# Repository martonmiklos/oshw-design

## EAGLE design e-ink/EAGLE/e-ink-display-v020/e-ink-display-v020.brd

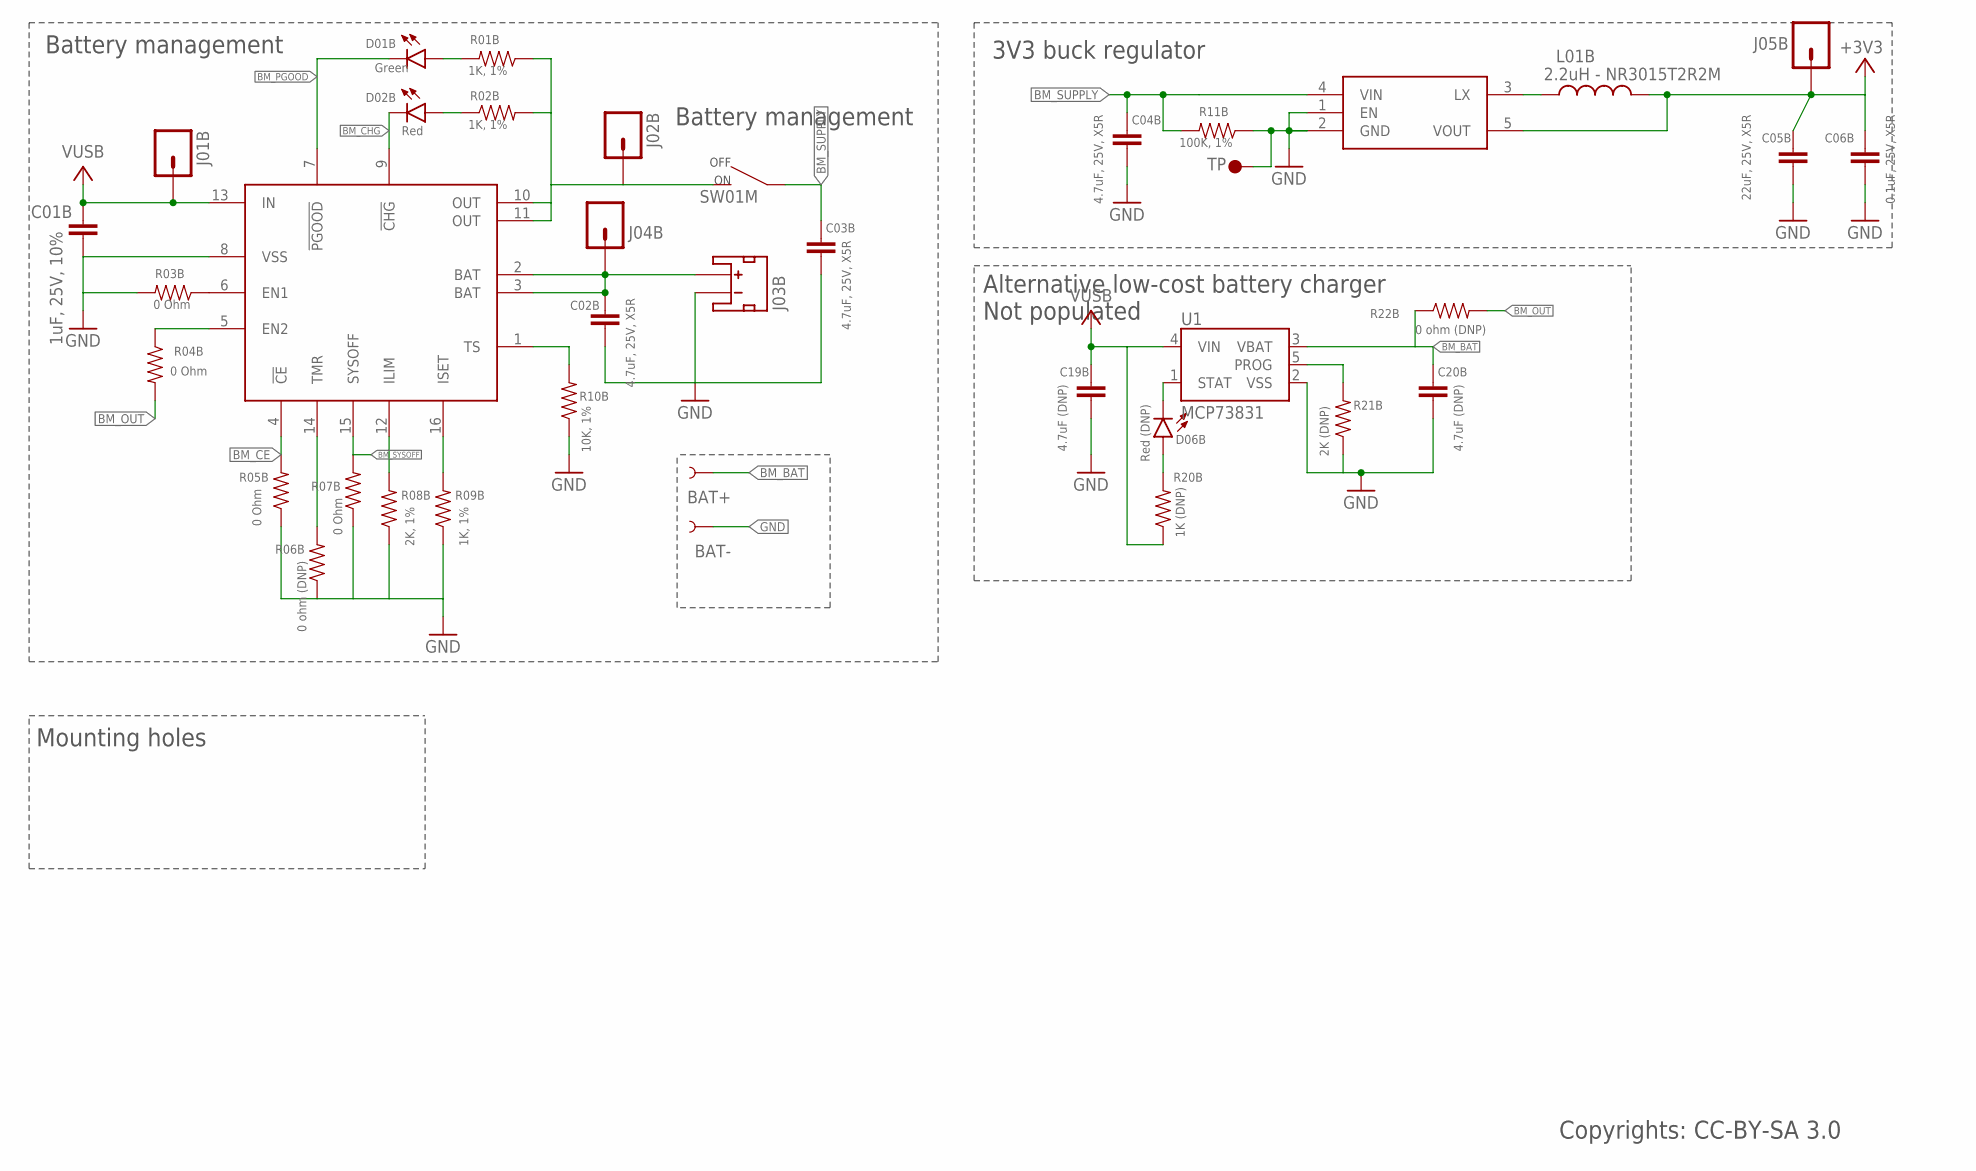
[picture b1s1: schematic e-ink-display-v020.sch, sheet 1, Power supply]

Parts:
BAT+: TEST-POINTSQ_THRU; TP-SQ_15TH
BAT-: TEST-POINTRD_THRU; TP-RD_15TH
C01B: 1uF, 25V, 10%; 0603-CAP
C02B, C03B, C04B: 4.7uF, 25V, X5R; 0603-CAP
C05B: 22uF, 25V, X5R; 0603-CAP
C06B: 0.1uF, 25V, X5R; 0603-CAP
C19B, C20B: 4.7uF (DNP); 0603-CAP
D01B: Green; LED-0603
D02B: Red; LED-0603
D06B: Red (DNP); LED-0603
J01B, J02B, J04B, J05B: M01PTH; 1X01
J03B: JST_2MM_MALE; JST-2-SMD
L01B: 2.2uH - NR3015T2R2M; INDUCTOR-NR3015
R01B, R02B, R09B: 1K, 1%; 0603-RES
R03B, R04B, R05B, R07B: 0 Ohm; 0603-RES
R06B: 0 ohm (DNP); 0603-RES
R08B: 2K, 1%; 0603-RES
R10B: 10K, 1%; 0603-RES
R11B: 100K, 1%; 0603-RES
R20B: 1K (DNP); 0603-RES
R21B: 2K (DNP); 0603-RES
R22B: 0 ohm (DNP); 1206
SW01M: SWITCHSIDE-SLIDE; SW-SPDT-TH
TP01B: TP1; TP35_BOT
U1: MCP73831; SOT23-5
U01B: BQ24075; PVQFN-16
U02B: R8008-33; SOT23-5

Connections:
+3V3: C05B.2, C06B.2, J05B.1, L01B.2, U02B.5 (VOUT); also elsewhere on the board
BM_BAT: BAT+.P$1, C02B.2, C20B.2, J03B.2 (+), J04B.1, R22B.1, U1.3 (VBAT), U01B.2 (BAT), U01B.3 (BAT)
BM_CE: R05B.2, U01B.4 (!CE)
BM_CHG: D02B.C, U01B.9 (!CHG); also elsewhere on the board
BM_OUT: J02B.1, R01B.1, R02B.2, R04B.2, R22B.2, SW01M.2, U01B.10 (OUT), U01B.11 (OUT)
BM_PGOOD: D01B.C, U01B.7 (!PGOOD); also elsewhere on the board
BM_SUPPLY: C03B.2, C04B.2, R11B.2, SW01M.1, U02B.4 (VIN); also elsewhere on the board
BM_SYSOFF: R07B.2, U01B.15 (SYSOFF)
GND: BAT-.P$1, C01B.1, C02B.1, C03B.1, C04B.1, C05B.1, C06B.1, C19B.1, C20B.1, J03B.1 (-), R03B.2, R05B.1, R06B.1, R07B.1, R08B.1, R09B.1, R10B.1, R11B.1, R21B.1, TP01B.P$1, U1.2 (VSS), U01B.8 (VSS), U02B.1 (EN), U02B.2 (GND); also elsewhere on the board
unnamed: R08B.2, U01B.12 (ILIM)
unnamed: R09B.2, U01B.16 (ISET)
unnamed: R04B.1, U01B.5 (EN2)
unnamed: R03B.1, U01B.6 (EN1)
unnamed: R06B.2, U01B.14 (TMR)
unnamed: R10B.2, U01B.1 (TS)
unnamed: D02B.A, R02B.1
unnamed: D01B.A, R01B.2
unnamed: R21B.2, U1.5 (PROG)
unnamed: L01B.1, U02B.3 (LX)
unnamed: D06B.C, U1.1 (STAT)
unnamed: D06B.A, R20B.2
VUSB: C01B.2, C19B.2, J01B.1, R20B.1, U1.4 (VIN), U01B.13 (IN); also elsewhere on the board

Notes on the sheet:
Battery management
3V3 buck regulator
Mounting holes
Alternative low-cost battery charger Not populated
Copyrights: CC-BY-SA 3.0

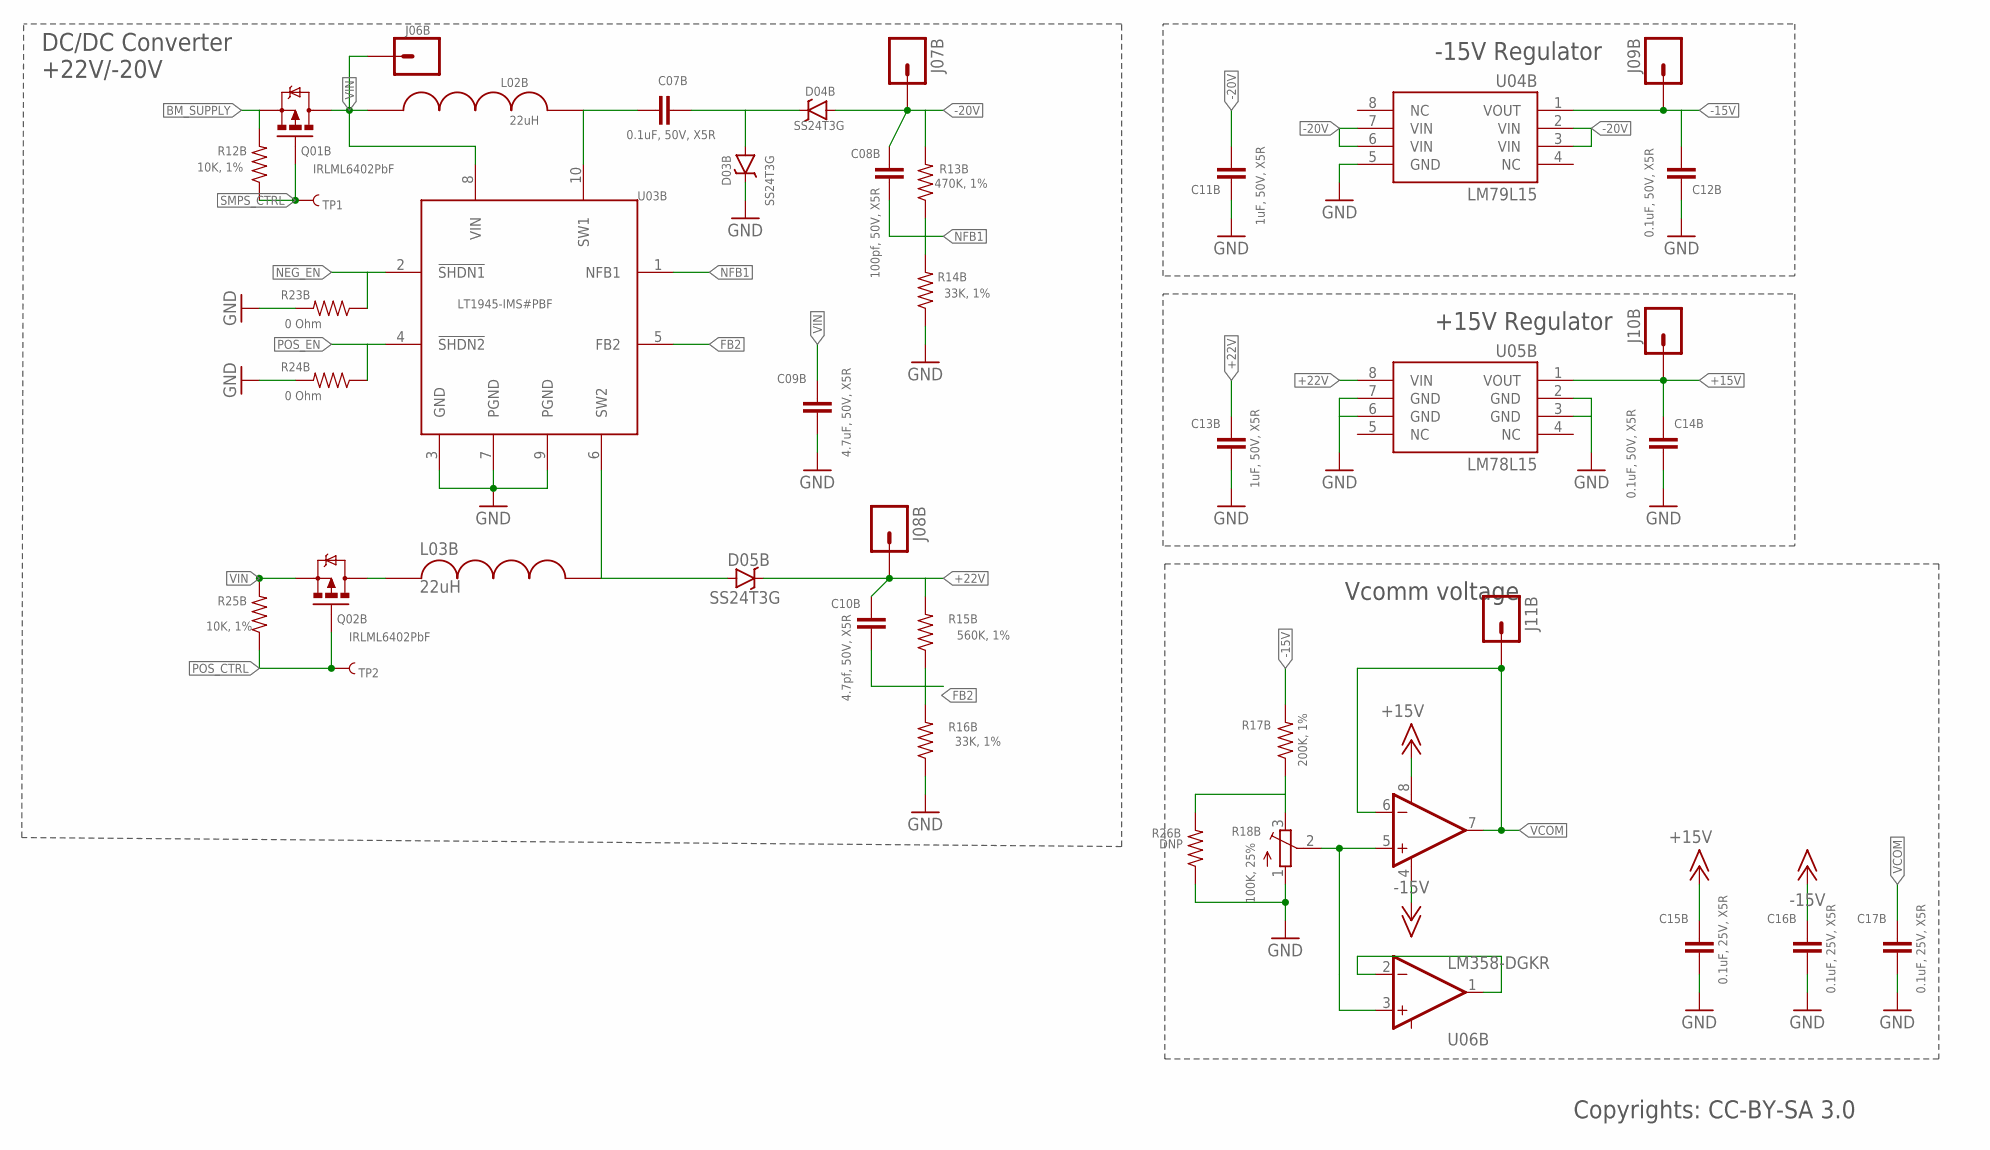
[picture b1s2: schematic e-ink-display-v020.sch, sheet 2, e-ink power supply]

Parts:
C07B, C12B, C14B: 0.1uF, 50V, X5R; 0603-CAP
C08B: 100pf, 50V, X5R; 0603-CAP
C09B: 4.7uF, 50V, X5R; 0603-CAP
C10B: 4.7pf, 50V, X5R; 0603-CAP
C11B, C13B: 1uF, 50V, X5R; 0603-CAP
C15B, C16B, C17B: 0.1uF, 25V, X5R; 0603-CAP
D03B, D04B, D05B: SS24T3G; SMA-DIODE
J06B, J07B, J08B, J09B, J10B, J11B: M01PTH; 1X01
L02B, L03B: 22uH; 4040(1515)
Q01B, Q02B: IRLML6402PbF; SOT23-3
R12B, R25B: 10K, 1%; 0603-RES
R13B: 470K, 1%; 0603-RES
R14B, R16B: 33K, 1%; 0603-RES
R15B: 560K, 1%; 0603-RES
R17B: 200K, 1%; 0603-RES
R18B: 100K, 25%; TC33X
R23B, R24B: 0 Ohm; 0603-RES
R26B: DNP; 0603-RES
TP1, TP2: TEST-POINTRD_THRU; TP-RD_15TH
U03B: LT1945-IMS#PBF; MSOP-10
U04B: LM79L15; SO08
U05B: LM78L15; SO08
U06B: LM358-DGKR; MSOP-8

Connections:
+15V: C14B.2, C15B.2, J10B.1, U05B.1 (VOUT), U06B.8 (V+); also elsewhere on the board
+22V: C10B.2, C13B.2, D05B.C, J08B.1, R15B.2, U05B.8 (VIN); also elsewhere on the board
-15V: C12B.2, C16B.2, J09B.1, R17B.2, U04B.1 (VOUT), U06B.4 (V-); also elsewhere on the board
-20V: C08B.2, C11B.2, D04B.A, J07B.1, R13B.2, U04B.2 (VIN), U04B.3 (VIN), U04B.6 (VIN), U04B.7 (VIN); also elsewhere on the board
BM_SUPPLY: Q01B.2 (S), R12B.2; also elsewhere on the board
FB2: C10B.1, R15B.1, R16B.2, U03B.5 (FB2)
GND: C09B.1, C11B.1, C12B.1, C13B.1, C14B.1, C15B.1, C16B.1, C17B.1, D03B.C, R14B.1, R16B.1, R18B.1 (A), R23B.2, R24B.2, R26B.1, U03B.3 (GND), U03B.7 (PGND), U03B.9 (PGND), U04B.5 (GND), U05B.2 (GND), U05B.3 (GND), U05B.6 (GND), U05B.7 (GND); also elsewhere on the board
unnamed: C07B.1, L02B.P$2, U03B.10 (SW1)
unnamed: C07B.2, D03B.A, D04B.C
unnamed: R18B.2 (S), U06B.3 (+IN1), U06B.5 (+IN2)
unnamed: D05B.A, L03B.P$2, U03B.6 (SW2)
unnamed: U06B.1 (OUT1), U06B.2 (-IN1)
unnamed: L03B.P$1, Q02B.3 (D)
unnamed: R17B.1, R18B.3 (E), R26B.2
NEG_EN: R23B.1, U03B.2 (!SHDN1); also elsewhere on the board
NFB1: C08B.1, R13B.1, R14B.2, U03B.1 (NFB1)
POS_CTRL: Q02B.1 (G), R25B.1, TP2.P$1; also elsewhere on the board
POS_EN: R24B.1, U03B.4 (!SHDN2); also elsewhere on the board
SMPS_CTRL: Q01B.1 (G), R12B.1, TP1.P$1; also elsewhere on the board
VCOM: C17B.2, J11B.1, U06B.6 (-IN2), U06B.7 (OUT2); also elsewhere on the board
VIN: C09B.2, J06B.1, L02B.P$1, Q01B.3 (D), Q02B.2 (S), R25B.2, U03B.8 (VIN)

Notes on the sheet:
-15V Regulator
+15V Regulator
Vcomm voltage
DC/DC Converter +22V/-20V
Copyrights: CC-BY-SA 3.0

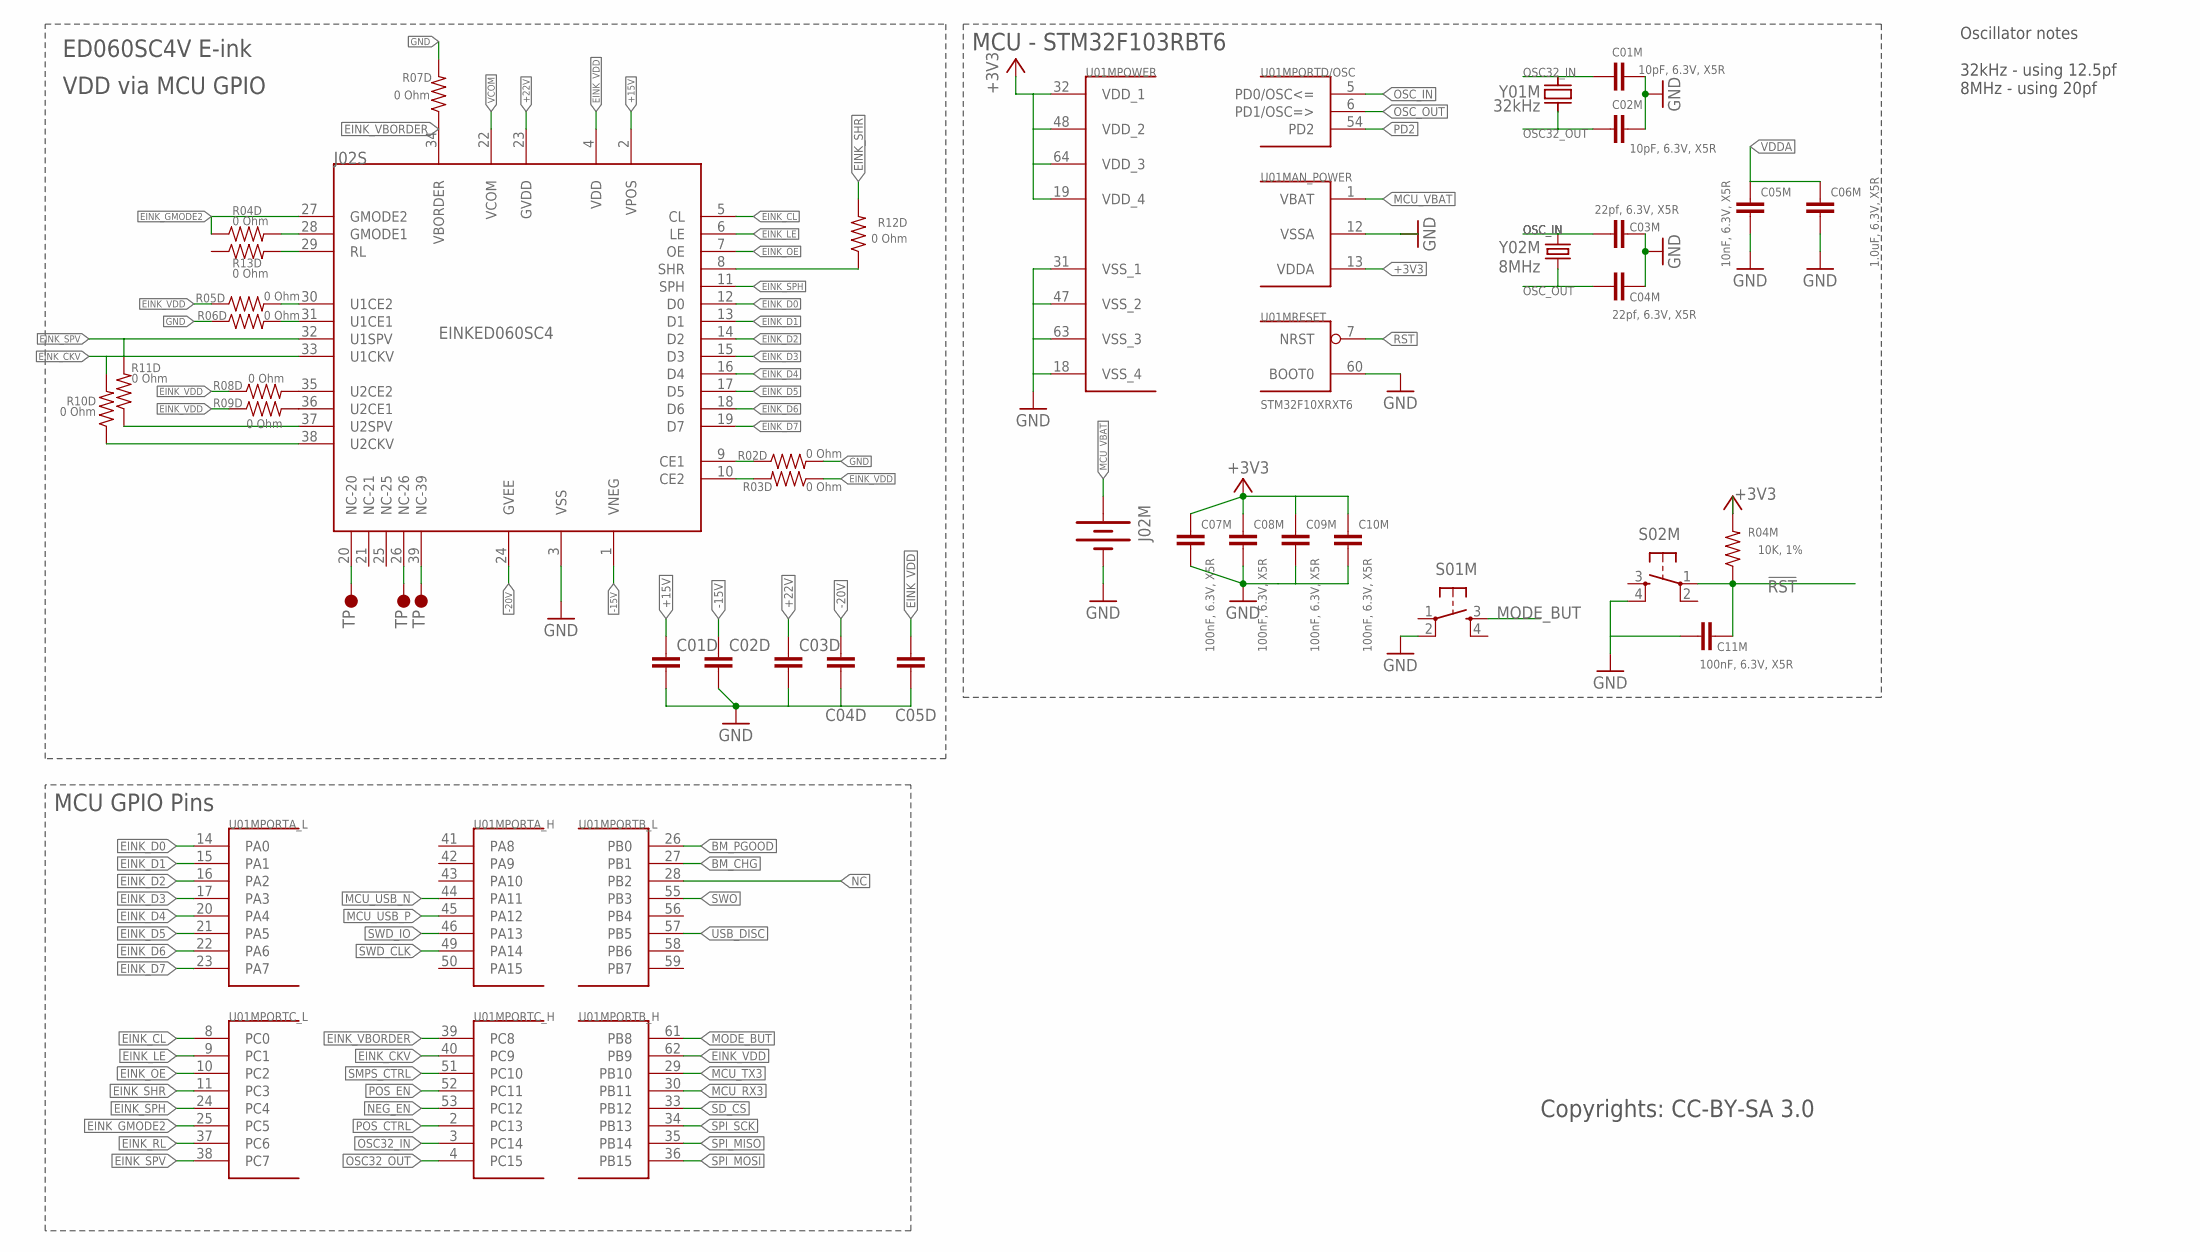
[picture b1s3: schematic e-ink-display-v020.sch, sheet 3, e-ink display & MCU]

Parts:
C01D, C02D, C03D, C04D, C05D: 100nF; 0603-CAP
C01M, C02M: 10pF, 6.3V, X5R; 0603-CAP
C03M, C04M: 22pf, 6.3V, X5R; 0603-CAP
C05M: 10nF, 6.3V, X5R; 0603-CAP
C06M: 1.0uF, 6.3V, X5R; 0603-CAP
C07M, C08M, C09M, C10M, C11M: 100nF, 6.3V, X5R; 0603-CAP
J02M: BATTERY20PTH; BATTCOM_20MM_PTH
J02S: EINKED060SC4; FPC-0.3-39
R02D, R03D, R04D, R05D, R06D, R07D, R08D, R09D, R10D, R11D, R12D, R13D: 0 Ohm; 0603-RES
R04M: 10K, 1%; 0603-RES
S01M, S02M: TAC_SWITCHSMD; TACTILE_SWITCH_SMD
U01M: STM32F10XRXT6; TQFP64
U$1, U$8, U$9: TP1; TP35_BOT
Y01M: 32kHz; FC135
Y02M: 8MHz; CRYSTAL-SMD-5X3

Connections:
!RST: C11M.1, R04M.1, S02M.1, U01M.7 (NRST); also elsewhere on the board
+3V3: C07M.1, C08M.1, C09M.1, C10M.1, R04M.2, U01M.13 (VDDA), U01M.19 (VDD_4), U01M.32 (VDD_1), U01M.48 (VDD_2), U01M.64 (VDD_3); also elsewhere on the board
+15V: C01D.1, J02S.2 (VPOS); also elsewhere on the board
+22V: C03D.1, J02S.23 (GVDD); also elsewhere on the board
-15V: C02D.1, J02S.1 (VNEG); also elsewhere on the board
-20V: C04D.1, J02S.24 (GVEE); also elsewhere on the board
BM_CHG: U01M.27 (PB1); also elsewhere on the board
BM_PGOOD: U01M.26 (PB0); also elsewhere on the board
CE2: J02S.10 (CE2), R03D.2
EINK_CKV: J02S.33 (U1CKV), R10D.2, U01M.40 (PC9); also elsewhere on the board
EINK_CL: J02S.5 (CL), U01M.8 (PC0); also elsewhere on the board
EINK_D0: J02S.12 (D0), U01M.14 (PA0); also elsewhere on the board
EINK_D1: J02S.13 (D1), U01M.15 (PA1); also elsewhere on the board
EINK_D2: J02S.14 (D2), U01M.16 (PA2); also elsewhere on the board
EINK_D3: J02S.15 (D3), U01M.17 (PA3); also elsewhere on the board
EINK_D4: J02S.16 (D4), U01M.20 (PA4); also elsewhere on the board
EINK_D5: J02S.17 (D5), U01M.21 (PA5); also elsewhere on the board
EINK_D6: J02S.18 (D6), U01M.22 (PA6); also elsewhere on the board
EINK_D7: J02S.19 (D7), U01M.23 (PA7); also elsewhere on the board
EINK_GMODE2: J02S.27 (GMODE2), R04D.1, U01M.25 (PC5); also elsewhere on the board
EINK_LE: J02S.6 (LE), U01M.9 (PC1); also elsewhere on the board
EINK_OE: J02S.7 (OE), U01M.10 (PC2); also elsewhere on the board
EINK_RL: U01M.37 (PC6); also elsewhere on the board
EINK_SHR: R12D.2, U01M.11 (PC3); also elsewhere on the board
EINK_SPH: J02S.11 (SPH), U01M.24 (PC4); also elsewhere on the board
EINK_SPV: J02S.32 (U1SPV), R11D.2, U01M.38 (PC7); also elsewhere on the board
EINK_VBORDER: J02S.34 (VBORDER), R07D.1, U01M.39 (PC8); also elsewhere on the board
EINK_VDD: C05D.1, J02S.4 (VDD), R03D.1, R05D.1, R08D.1, R09D.1, U01M.62 (PB9); also elsewhere on the board
GND: C01D.2, C01M.2, C02D.2, C02M.2, C03D.2, C03M.2, C04D.2, C04M.2, C05D.2, C05M.2, C06M.2, C07M.2, C08M.2, C09M.2, C10M.2, C11M.2, J02M.2 (-), J02S.3 (VSS), R02D.2, R06D.1, R07D.2, S01M.2, S02M.4, U01M.12 (VSSA), U01M.18 (VSS_4), U01M.31 (VSS_1), U01M.47 (VSS_2), U01M.60 (BOOT0), U01M.63 (VSS_3); also elsewhere on the board
MCU_RX3: U01M.30 (PB11); also elsewhere on the board
MCU_TX3: U01M.29 (PB10); also elsewhere on the board
MCU_USB_N: U01M.44 (PA11); also elsewhere on the board
MCU_USB_P: U01M.45 (PA12); also elsewhere on the board
MCU_VBAT: J02M.1 (+), U01M.1 (VBAT)
MODE_BUT: S01M.3, U01M.61 (PB8)
unnamed: J02S.28 (GMODE1), R04D.2
unnamed: J02S.31 (U1CE1), R06D.2
unnamed: J02S.29 (RL), R13D.2
unnamed: J02S.35 (U2CE2), R08D.2
unnamed: J02S.36 (U2CE1), R09D.2
unnamed: J02S.9 (CE1), R02D.1
unnamed: J02S.20 (NC-20), U$1.P$1
unnamed: J02S.26 (NC-26), U$8.P$1
unnamed: J02S.8 (SHR), R12D.1
unnamed: J02S.39 (NC-39), U$9.P$1
NC: U01M.28 (PB2)
NEG_EN: U01M.53 (PC12); also elsewhere on the board
OSC32_IN: C01M.1, U01M.3 (PC14), Y01M.X2 (2)
OSC32_OUT: C02M.1, U01M.4 (PC15), Y01M.X1 (1)
OSC_IN: C03M.1, U01M.5 (PD0/OSC<=), Y02M.3 (2)
OSC_OUT: C04M.1, U01M.6 (PD1/OSC=>), Y02M.1
PD2: U01M.54 (PD2)
POS_CTRL: U01M.2 (PC13); also elsewhere on the board
POS_EN: U01M.52 (PC11); also elsewhere on the board
SD_CS: U01M.33 (PB12); also elsewhere on the board
SMPS_CTRL: U01M.51 (PC10); also elsewhere on the board
SPI_MISO: U01M.35 (PB14); also elsewhere on the board
SPI_MOSI: U01M.36 (PB15); also elsewhere on the board
SPI_SCK: U01M.34 (PB13); also elsewhere on the board
SWD_CLK: U01M.49 (PA14); also elsewhere on the board
SWD_IO: U01M.46 (PA13); also elsewhere on the board
SWO: U01M.55 (PB3); also elsewhere on the board
U1CE2: J02S.30 (U1CE2), R05D.2
U2CKV: J02S.38 (U2CKV), R10D.1
U2SPV: J02S.37 (U2SPV), R11D.1
USB_DISC: U01M.57 (PB5); also elsewhere on the board
VCOM: J02S.22 (VCOM); also elsewhere on the board
VDDA: C05M.1, C06M.1

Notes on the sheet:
ED060SC4V E-ink VDD via MCU GPIO
MCU - STM32F103RBT6
Copyrights: CC-BY-SA 3.0
MCU GPIO Pins
Oscillator notes 32kHz - using 12.5pf 8MHz - using 20pf

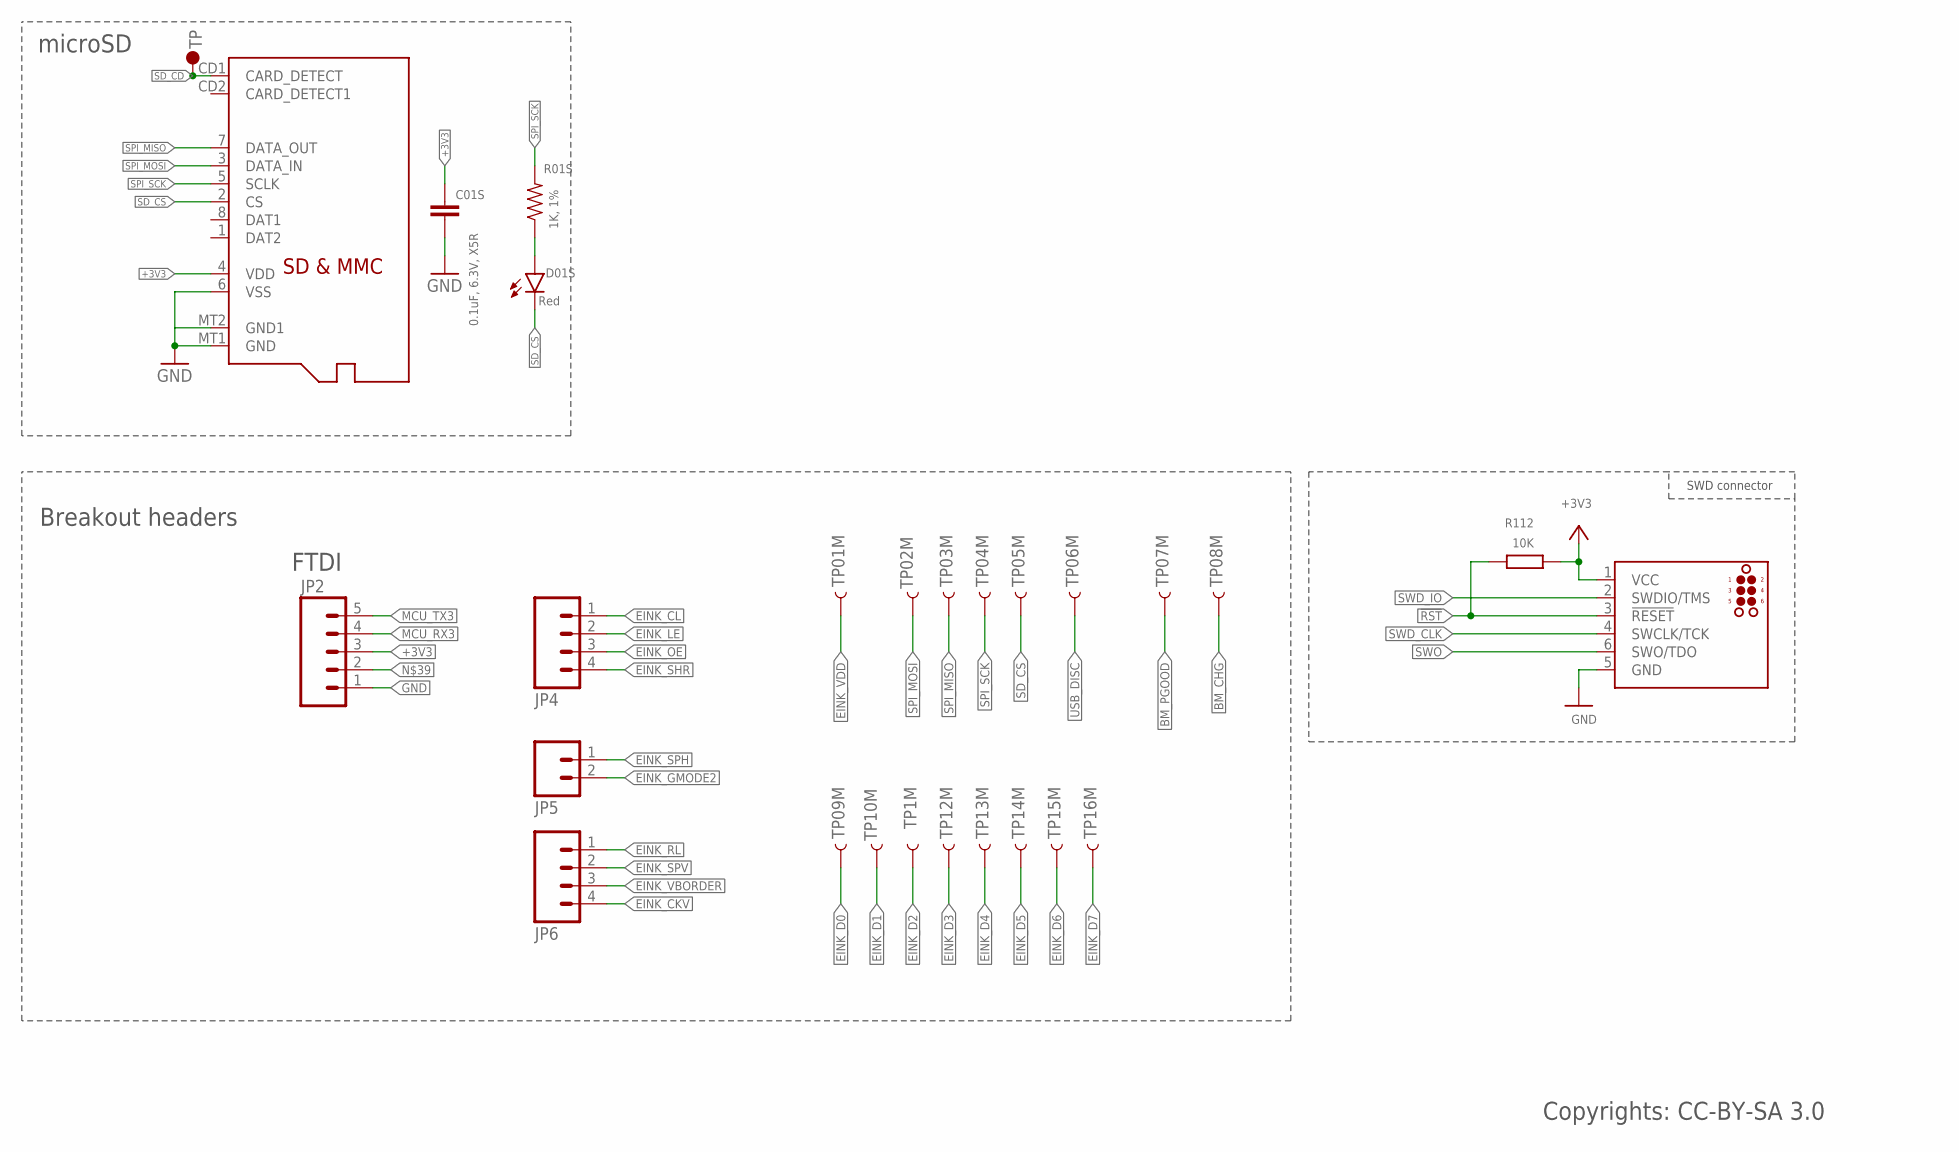
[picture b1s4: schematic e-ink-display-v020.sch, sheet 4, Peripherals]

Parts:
C01S: 0.1uF, 6.3V, X5R; 0603-CAP
D01S: Red; LED-0603
J1: TC2030_SWD-MCP-NL; TC2030-MCP-NL
J01S: MICROSD
JP2: M05PTH; 1X05
JP4, JP6: M04PTH; 1X04
JP5: M02PTH; 1X02
R01S: 1K, 1%; 0603-RES
R112: 10K; R0603
TP1M, TP01M, TP02M, TP04M, TP05M, TP06M, TP07M, TP08M, TP09M, TP10M, TP12M, TP13M, TP14M, TP15M, TP16M: TEST-POINTRD_THRU; TP-RD_15TH
TP03M: TEST-POINTTP_15TH_THRU; TP_15TH
U$5: TP3; TP60_BOT

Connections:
!RST: J1.3 (!RESET), R112.2; also elsewhere on the board
+3V3: C01S.1, J1.1 (VCC), J01S.4 (VDD), JP2.3, R112.1; also elsewhere on the board
BM_CHG: TP08M.P$1; also elsewhere on the board
BM_PGOOD: TP07M.P$1; also elsewhere on the board
EINK_CKV: JP6.4; also elsewhere on the board
EINK_CL: JP4.1; also elsewhere on the board
EINK_D0: TP09M.P$1; also elsewhere on the board
EINK_D1: TP10M.P$1; also elsewhere on the board
EINK_D2: TP1M.P$1; also elsewhere on the board
EINK_D3: TP12M.P$1; also elsewhere on the board
EINK_D4: TP13M.P$1; also elsewhere on the board
EINK_D5: TP14M.P$1; also elsewhere on the board
EINK_D6: TP15M.P$1; also elsewhere on the board
EINK_D7: TP16M.P$1; also elsewhere on the board
EINK_GMODE2: JP5.2; also elsewhere on the board
EINK_LE: JP4.2; also elsewhere on the board
EINK_OE: JP4.3; also elsewhere on the board
EINK_RL: JP6.1; also elsewhere on the board
EINK_SHR: JP4.4; also elsewhere on the board
EINK_SPH: JP5.1; also elsewhere on the board
EINK_SPV: JP6.2; also elsewhere on the board
EINK_VBORDER: JP6.3; also elsewhere on the board
EINK_VDD: TP01M.P$1; also elsewhere on the board
GND: C01S.2, J1.5 (GND), J01S.6 (VSS), J01S.MT1 (GND), J01S.MT2 (GND1), JP2.1; also elsewhere on the board
MCU_RX3: JP2.4; also elsewhere on the board
MCU_TX3: JP2.5; also elsewhere on the board
R01S: D01S.A, R01S.1
SD_CD: J01S.CD1 (CARD_DETECT), U$5.P$1
SD_CS: D01S.C, J01S.2 (CS), TP05M.P$1; also elsewhere on the board
SPI_MISO: J01S.7 (DATA_OUT), TP03M.P$1; also elsewhere on the board
SPI_MOSI: J01S.3 (DATA_IN), TP02M.P$1; also elsewhere on the board
SPI_SCK: J01S.5 (SCLK), R01S.2, TP04M.P$1; also elsewhere on the board
SWD_CLK: J1.4 (SWCLK/TCK); also elsewhere on the board
SWD_IO: J1.2 (SWDIO/TMS); also elsewhere on the board
SWO: J1.6 (SWO/TDO); also elsewhere on the board
USB_DISC: TP06M.P$1; also elsewhere on the board

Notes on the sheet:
microSD
Copyrights: CC-BY-SA 3.0
FTDI
Breakout headers
SWD connector

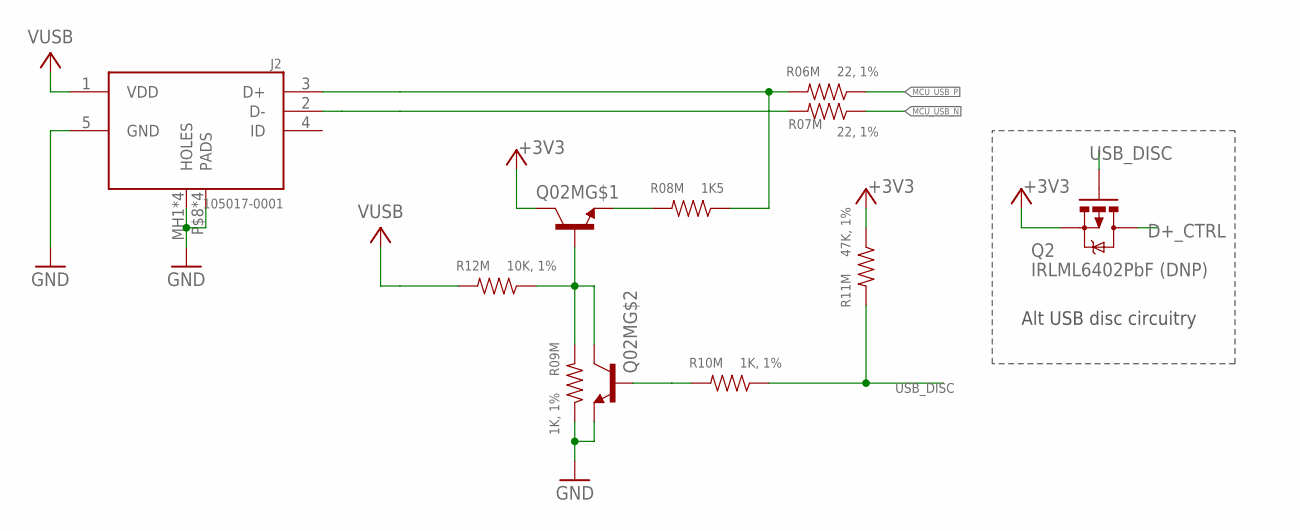
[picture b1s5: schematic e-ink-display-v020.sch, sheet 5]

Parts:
J2: 105017-0001; MOLEX_105017-0001
Q2: IRLML6402PbF (DNP); SOT23-3
Q02M: MMDT3904; SOT363
R06M, R07M: 22, 1%; 0603-RES
R08M: 1K5; 0603-RES
R09M, R10M: 1K, 1%; 0603-RES
R11M: 47K, 1%; 0603-RES
R12M: 10K, 1%; 0603-RES

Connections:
+3V3: Q2.2 (S), Q02M.6 (C), R11M.1; also elsewhere on the board
D+_CTRL: Q2.3 (D), Q02M.1 (E), R08M.2
GND: J2.5 (GND), J2.MH1 (HOLES), J2.MH2 (HOLES), J2.MH3 (HOLES), J2.MH4 (HOLES), J2.P$8 (PADS), J2.P$9 (PADS), J2.P$10 (PADS), J2.P$11 (PADS), Q02M.4 (E), R09M.1; also elsewhere on the board
MCU_USB_N: R07M.1; also elsewhere on the board
MCU_USB_P: R06M.1; also elsewhere on the board
MCU_USB_R_N: J2.2 (D-), R07M.2
MCU_USB__R_P: J2.3 (D+), R06M.2, R08M.1
unnamed: Q02M.2 (B), Q02M.3 (C), R09M.2, R12M.1
unnamed: Q02M.5 (B), R10M.2
USB_DISC: Q2.1 (G), R10M.1, R11M.2; also elsewhere on the board
VUSB: J2.1 (VDD), R12M.2; also elsewhere on the board

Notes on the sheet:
Alt USB disc circuitry

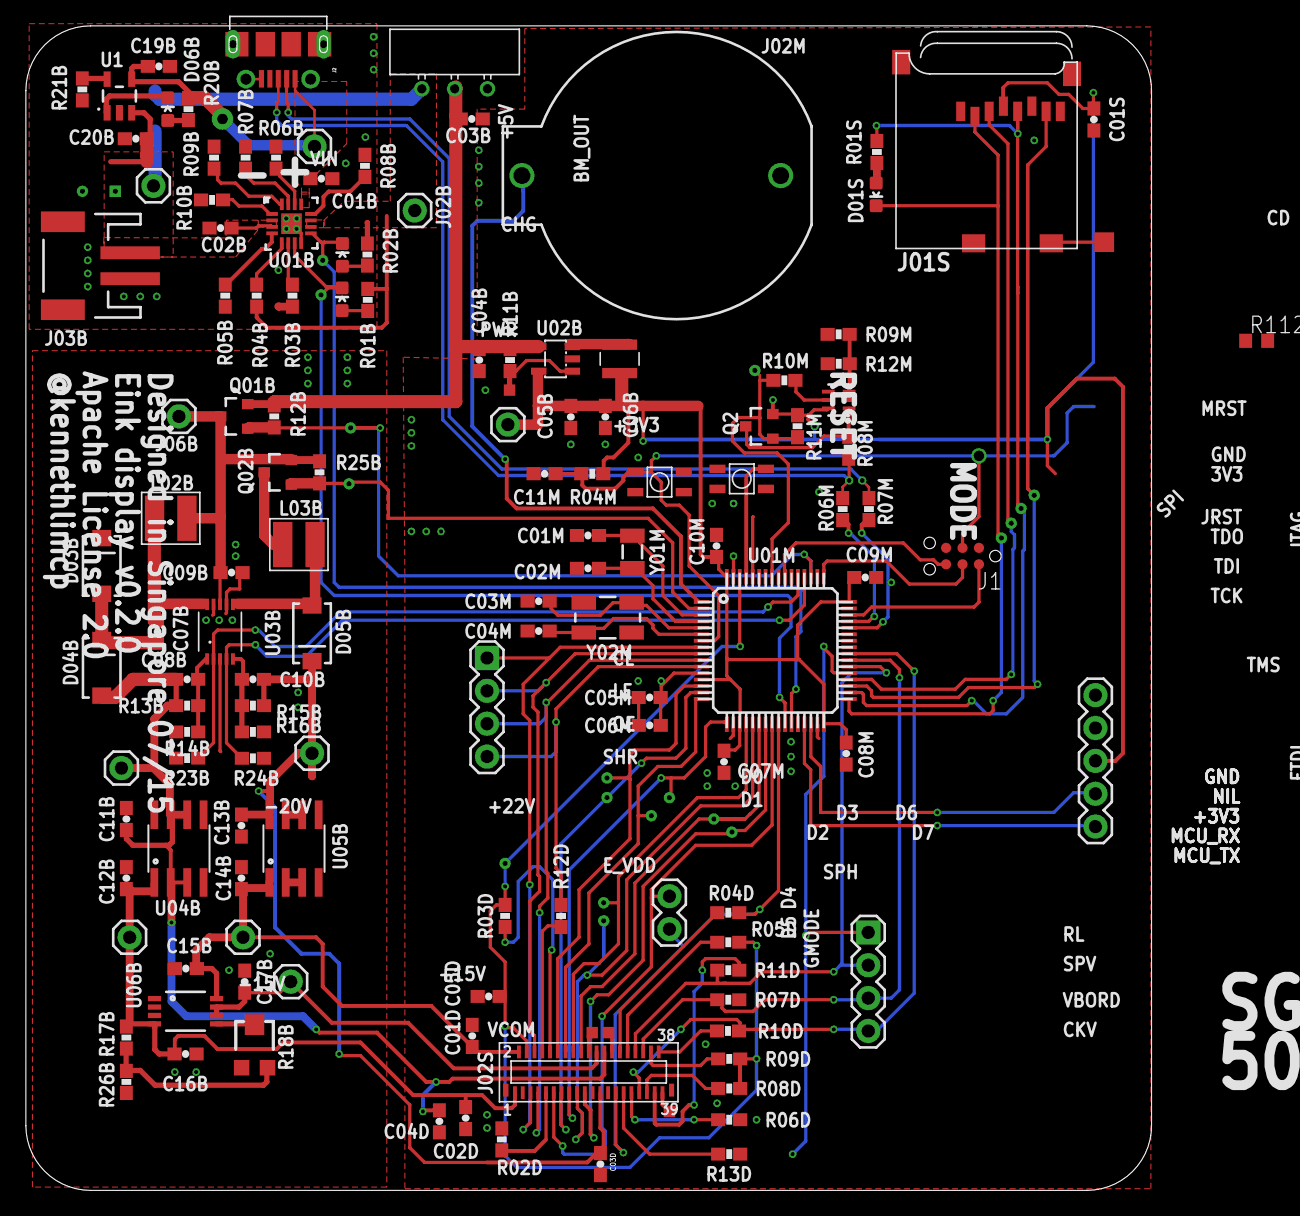
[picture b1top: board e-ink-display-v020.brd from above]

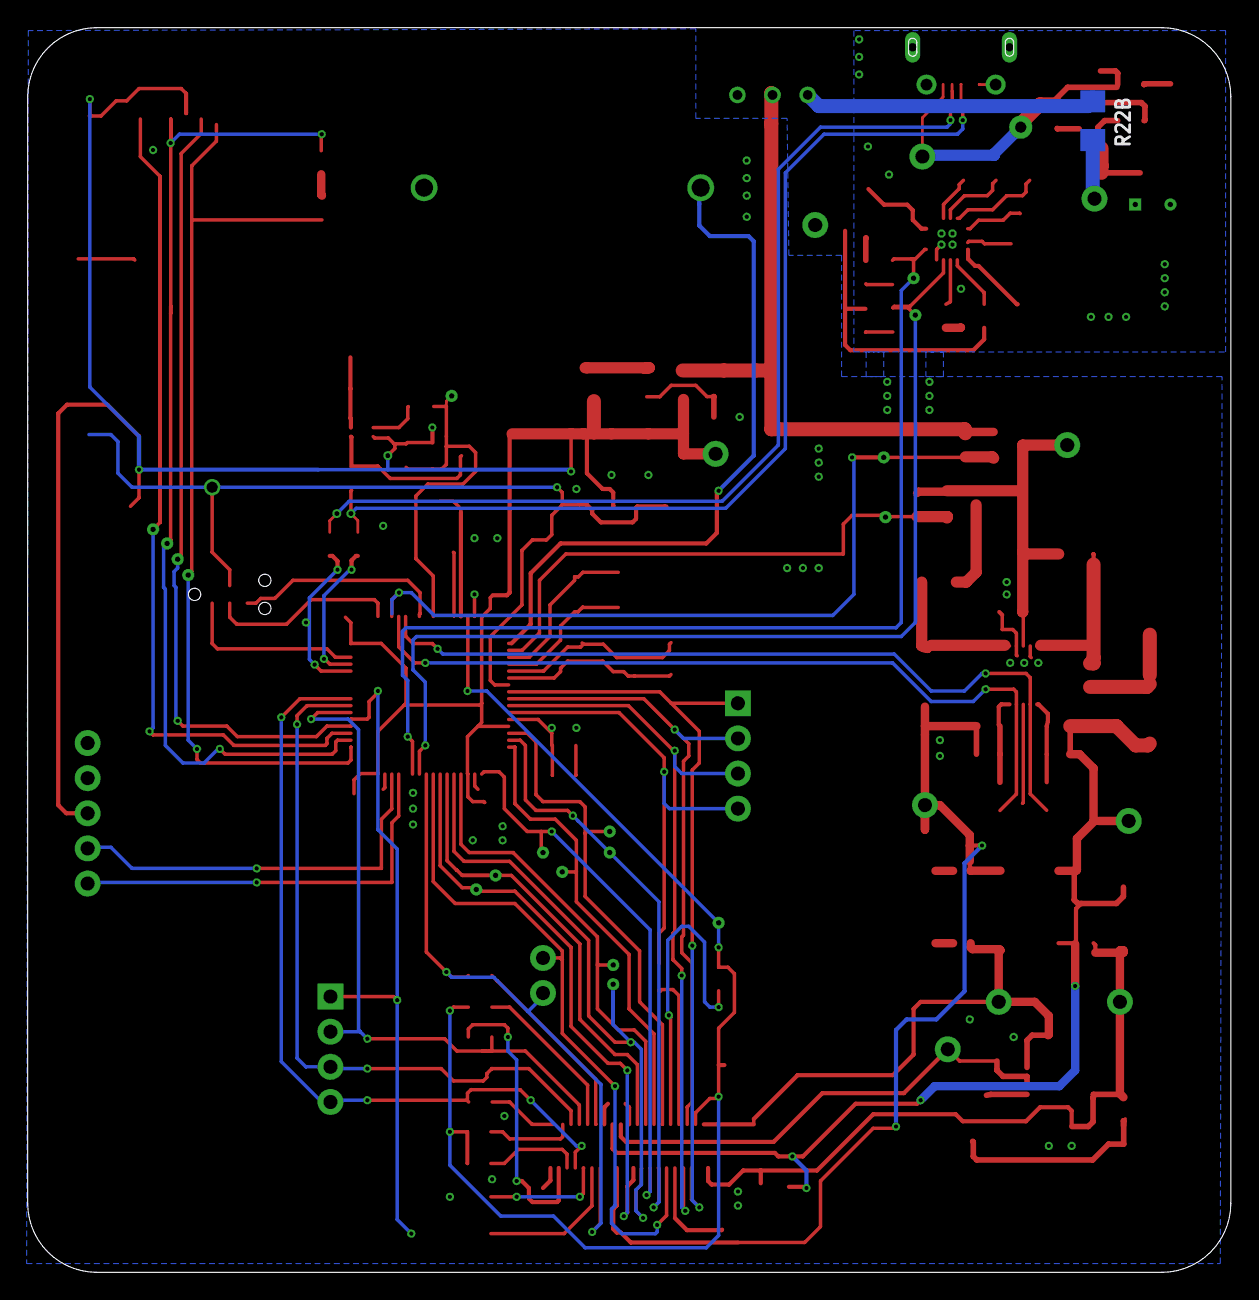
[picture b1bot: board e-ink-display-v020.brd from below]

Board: 2 copper layers, 87.0 x 90.0 mm, 155 parts (6 on the bottom side), 101 nets.

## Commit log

2019-09-29 Polishing e-ink-display-v020 to fit my personal taste

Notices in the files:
e-ink/EAGLE/e-ink-display-v020/e-ink-display-v020.brd:
Apache License 2.0
parts and their libraries:
SparkFun-Capacitors: Licensing: Creative Commons ShareAlike 4.0 International - https://creativecommons.org/licenses/by-sa/4.0
tag-connect: ©2009 ROFA.cz - modified and updated by Robert Darlington ‹rdarlington@gmail.com›
